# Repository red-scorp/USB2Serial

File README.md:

```
 __   __  _______  _______  _______  _______  _______  ______    ___   _______  ___     
|  | |  ||       ||  _    ||       ||       ||       ||    _ |  |   | |   _   ||   |    
|  | |  ||  _____|| |_|   ||____   ||  _____||    ___||   | ||  |   | |  |_|  ||   |    
|  |_|  || |_____ |       | ____|  || |_____ |   |___ |   |_||_ |   | |       ||   |    
|       ||_____  ||  _   | | ______||_____  ||    ___||    __  ||   | |       ||   |___ 
|       | _____| || |_|   || |_____  _____| ||   |___ |   |  | ||   | |   _   ||       |
|_______||_______||_______||_______||_______||_______||___|  |_||___| |__| |__||_______|
```

# USB2Serial project

USB to Serial board came as a helping board for my another my project.
I had to program a number of cheap Arduino Pro Mini clone boards in a row.
The problem I was having was to mix up cable all the time.
I decided to fix this issue once and for all by creating a simple USB to Serial interface board which will connect directly with Arduino Pro Mini correctly.

## USB2Serial_CH340G_v1.2

**USB2Serial_CH340G_v1.2** is a simple USB to Serial board based on CH340G chip, created especially to fit well with Arduino Pro Mini boards.

Preview:

[Schematics in PDF format](doc/USB2Serial_CH340G_v1.2.pdf)

Features:

- based on very cheap CH340G chip
- locked pins for Pro Mini
- configurable for 5V and 3.3V

CAM files are available.
BoM and PnP files for JLCPCB are available.

## USB2Serial_FT232RL_v1.0

**USB2Serial_FT232RL_v1.0** is a simple USB to Serial board based on FT232RL chip, created especially to fit well with Arduino Pro Mini boards.

Preview:

[Schematics in PDF format](doc/USB2Serial_FT232RL_v1.0.pdf)

Features:

- based on more common FT232RL chip
- locked pins for Pro Mini
- configurable for 5V and 3.3V

CAM files are available.
BoM and PnP files for JLCPCB are available.

## USB2Serial_CP2102_v1.0

**USB2Serial_CP2102_v1.0** is a simple USB to Serial board based on CP2102 chip, created especially to fit well with Arduino Pro Mini boards.

Preview:

[Schematics in PDF format](doc/USB2Serial_CP2102_v1.0.pdf)

Features:

- based on more common CP2102 chip
- locked pins for Pro Mini
- configurable for 5V and 3.3V

CAM files are available.
BoM and PnP files for JLCPCB are available.

## Links

- CH340G Driver for Windows: [CH341SER_ZIP](http://www.wch.cn/download/CH341SER_ZIP.html)
- FT232RL Driver for Windows: [Home/Drivers/VCP Drivers](https://ftdichip.com/drivers/vcp-drivers/)
- CP2102 Driver for Windows: [CP210x USB to UART Bridge VCP Drivers](https://www.silabs.com/developers/usb-to-uart-bridge-vcp-drivers)

## How to help

Your contributions as code, resources, or finances are welcome! Please contact me directly via email at andriy.golovnya@gmail.com or through my [GitHub profile](https://github.com/red-scorp).

If you'd like to make a financial contribution, you can donate via [PayPal](http://paypal.me/redscorp) or [Ko-Fi](http://ko-fi.com/redscorp). Your support is greatly appreciated.

Thanks in advance!

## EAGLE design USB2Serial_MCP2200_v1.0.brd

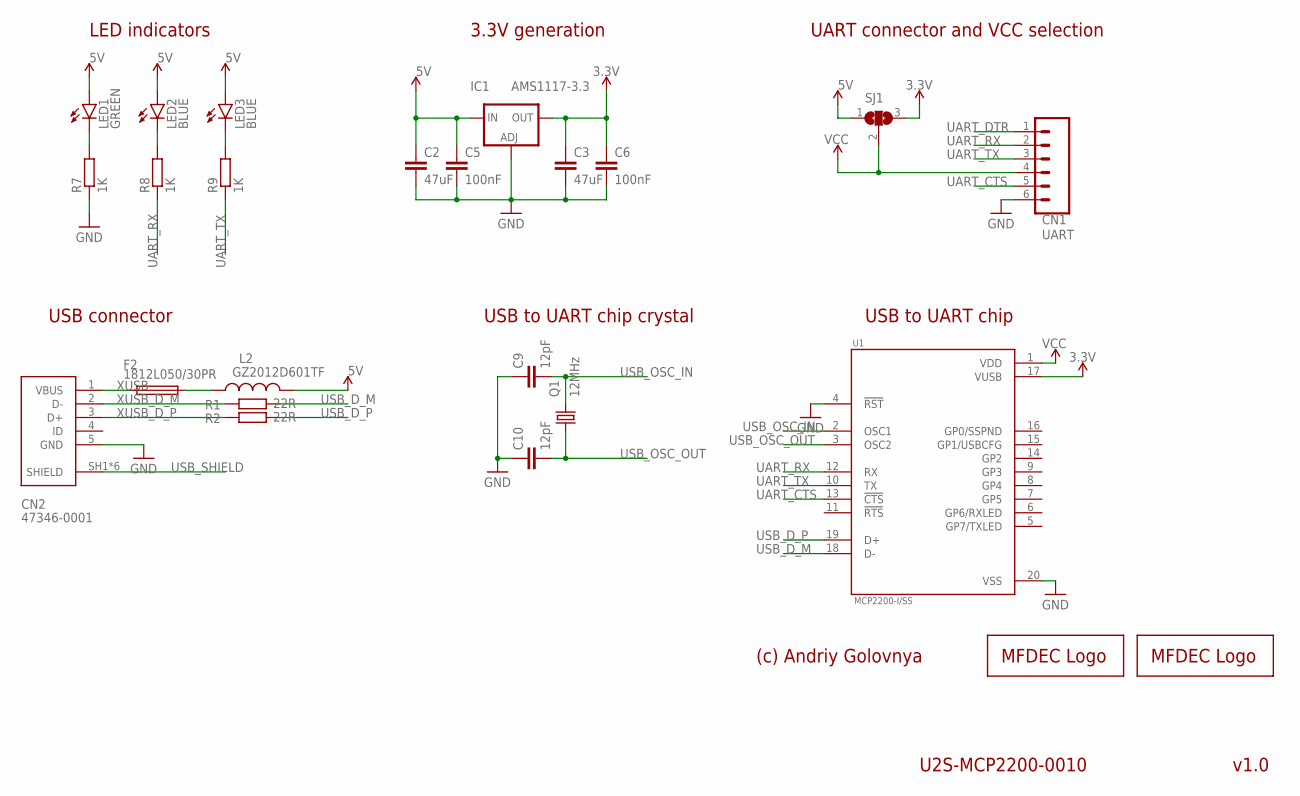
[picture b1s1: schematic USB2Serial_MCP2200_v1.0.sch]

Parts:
C2, C3: 47uF; C0805
C5, C6: 100nF; C0402
C9, C10: 12pF; C0402
CN1: UART; 1X06_LOCK
CN2: 47346-0001; MOLEX_47346-0001
F2: 1812L050/30PR; MF-SMDF050
IC1: AMS1117-3.3; SOT223
L2: GZ2012D601TF; WE-CBA_0805(W=4)
LED1: GREEN; SML0603
LED2, LED3: BLUE; SML0603
LOGO1: MFDECLOGO_L_20MM; MFDEC_L_20MM
LOGO2: MFDECLOGO_SQ_10MM; MFDEC_SQ_10MM
Q1: 12MHz; 3.2X2.5_KX-7
R1, R2: 22R; R0402
R7, R8, R9: 1K; R0402
SJ1: SJ2FI; SJ_2FI
U1: MCP2200-I/SS; SOP65P780X200-20N

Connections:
3.3V: C3.1, C6.1, IC1.4 (OUT), SJ1.3, U1.17 (VUSB)
5V: C2.1, C5.1, IC1.3 (IN), L2.2, LED1.A, LED2.A, LED3.A, SJ1.1
GND: C2.2, C3.2, C5.2, C6.2, C9.1, C10.1, CN1.6, CN2.5 (GND), IC1.1 (ADJ), R7.1, U1.4 (!RST), U1.20 (VSS)
unnamed: F2.2, L2.1
unnamed: LED1.C, R7.2
unnamed: LED3.C, R9.2
unnamed: LED2.C, R8.2
UART_CTS: CN1.5, U1.13 (!CTS)
UART_DTR: CN1.1
UART_RX: CN1.2, R8.1, U1.12 (RX)
UART_TX: CN1.3, R9.1, U1.10 (TX)
USB_D_M: R1.2, U1.18 (D-)
USB_D_P: R2.2, U1.19 (D+)
USB_OSC_IN: C9.2, Q1.3 (2), U1.2 (OSC1)
USB_OSC_OUT: C10.2, Q1.1, U1.3 (OSC2)
USB_SHIELD: CN2.SH1 (SHIELD), CN2.SH2 (SHIELD), CN2.SH3 (SHIELD), CN2.SH4 (SHIELD), CN2.SH5 (SHIELD), CN2.SH6 (SHIELD)
VCC: CN1.4, SJ1.2, U1.1 (VDD)
XUSB: CN2.1 (VBUS), F2.1
XUSB_D_M: CN2.2 (D-), R1.1
XUSB_D_P: CN2.3 (D+), R2.1

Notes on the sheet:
USB connector
USB to UART chip
USB to UART chip crystal
v1.0
3.3V generation
LED indicators
UART connector and VCC selection
(c) Andriy Golovnya
U2S-MCP2200-0010

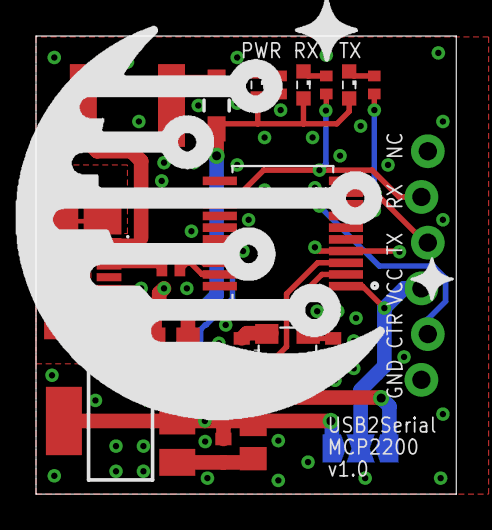
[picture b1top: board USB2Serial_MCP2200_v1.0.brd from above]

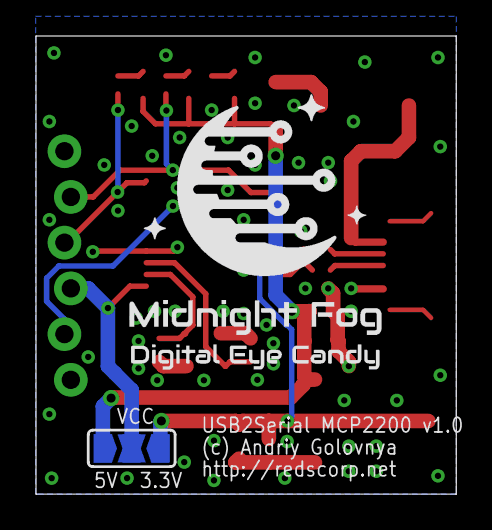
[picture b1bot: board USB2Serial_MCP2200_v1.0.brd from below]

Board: 2 copper layers, 23.3 x 25.5 mm, 24 parts (2 on the bottom side), 19 nets.

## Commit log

2020-10-19 Add initial design of USB2Serial based on CH340G
2020-10-19 Fix some names
2020-10-19 Add basic board design. Remove R3 as not strictly needed.
2020-10-20 Route the board. Add texts and logos
2020-10-20 Renamed files to keep a common naming convention
2020-10-22 Add JLCPCB Gerber, BOM and P&P files
2020-11-22 Add document number
2021-01-21 Fixed column name in BOM.
2021-01-21 Generated PNG preview. Generated PDF schematics.
2021-02-05 Added descriptions. Added FUNDING.yml.
2021-02-06 USB2Serial_CH340G_v1.1 files are added.
2021-02-06 Updated descriptions.
2021-02-06 Generated PDF schematics. Generated PNG preview image.
2021-02-06 Generated CAM.
2021-02-07 Removed pin headers contour from PCB v1.1. Generated PNG preview.
2021-04-06 Added FT232RL based board.
2021-04-07 Added C2. Added 1.2 for CH240G board.
2021-04-07 Minor changes
2021-04-08 Added CAM, preview and schematics.
2021-04-09 Minor changes. Generated new CAM.
2021-04-09 Updated descriptions
2021-04-10 Removed older CH340G boards.
2021-04-10 Fix description
2021-04-10 Added new BoM and PnP files (not tested yet)
2021-04-11 Fixed BOM and PnP files
2021-04-23 Added CP2102 board.
2021-04-24 Moved some traced around
2021-04-24 Generated PDF schematics. Generated PNG preview.
2021-04-24 Generated CAM files.
2021-04-25 Add BoM and PnP files for CP2102 board.
2021-04-25 Fixed BoM and PnP files for CH340G and FT232RL boards.
2021-12-05 cleanup.
2022-01-24 Added Ko-Fi link
2023-08-09 Added ASCII art banner
2023-08-09 First attempt to add MCP2200 based board from last year.

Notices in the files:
parts and their libraries:
Wurth_Automotive_WE-CBA: Copyright: Würth Elektronik
crystal-geyer_V1_0: Copyright: Geyer-Electronic
SparkFun-PowerSymbols: Licensing: Creative Commons ShareAlike 4.0 International - https://creativecommons.org/licenses/by-sa/4.0
